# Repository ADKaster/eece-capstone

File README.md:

# eece-capstone
Repository to store software work products for capstone.

## Project Overview

The communication library is the Distributed Microcontroller Communication Framework Library (dmcflib for short).

The end goal is to enable an application developer to use the publish-subscribe API presented in the library to easily send messages
between different microcontrollers in a system over I2C. The real demo application will be a telemetry system for an amateur rocket
with a Sensor, Data Logging, Power and Radio Communcations board. The project will be implemented using the TI Simplelink family
of ARM Cortex-M4F microcontrollers, with 3 MSP432s and one CC1310 Sub-1GHz MCU. 

## Configuration

Initial compilation and environment setup was tested using Ubuntu 14.04 LTS in an Oracle 
VirtualBox Virtual Machine, as well as Windows 10.

Theere are two main dependencies for this project. Code Composer Studio, and FreeRTOS.

### Code Composer Studio

The project requires TI's Code Composer Stuido Version 7 (ccsv7). This is necessary for
the cross-compiler as well as TI's SimpleLink SDK.

* Download Code composer studio version 7.x [here](http://processors.wiki.ti.com/index.php/Download_CCS)
* Ensure that Code Composer studio will be installed at ~/ti (or $HOME/ti or /home/<username>/ti) on linux, or C:/ti on Windows.
* Click the two checkboxes for SimpleLink MSP432 and SimpleLink CC13XX support.
* Perform all  other installation steps per TI's wiki as linked above
* On the "Getting Started" page, click the "Browse Examples" option to open the Resource Explorer. Alternatively, if the Resource Explorer is already open, navigate to that tab.
* Open the tree on the left side of the Resource Explorer titled "Software"
* Click the button that looks like a download button and download the MSP432 SDK v:1.60.00.12 "offline"

### FreeRTOS

FreeRTOS is used to manage task scheduling

* Download FreeRTOSv10.0.0 [here](http://www.freertos.org/a00104.html)
* Extract the archive to either your home directory on linux, or c:/ on Windows

### Adding the projects to Code Composer Studio

Steps to start working:
 
 * Clone the git repository to your favorite location

 * Download ccsv7 with MSP432 and CC13xx libraries
 	* /home/user/ti
 	* c:\ti
 
 * Install MSP432 simplelink sdk v1.60.00.12 from resource explorer
 
 * Install FreeRTOSv10.0.0
 	* /home/user/FreeRTOSv10.0.0
 	* c:\FreeRTOSv10.0.0
 
 * Open CCS and create a workspace in the same directory as the git repo
 
 * Go to Window-->Preferences-->General-->Workspace-->Linked Resources
     * New, Name = FREERTOS_INSTALL_DIR, Location = FreeRTOS Install Folder (with the vXX.XX.XX)
	 
 * Go to Project-->Import CCS Projects
     * Click Browse, Ok (Defaults to workspace directory)
	 * Check box next to all projects, click finish

 * Build the MSP432_example project, or your favorite application project	 
	
## Caveats
* Only configured to build for the MSP432. Additional tweaks and setup required to support CC13x0 boards. :(

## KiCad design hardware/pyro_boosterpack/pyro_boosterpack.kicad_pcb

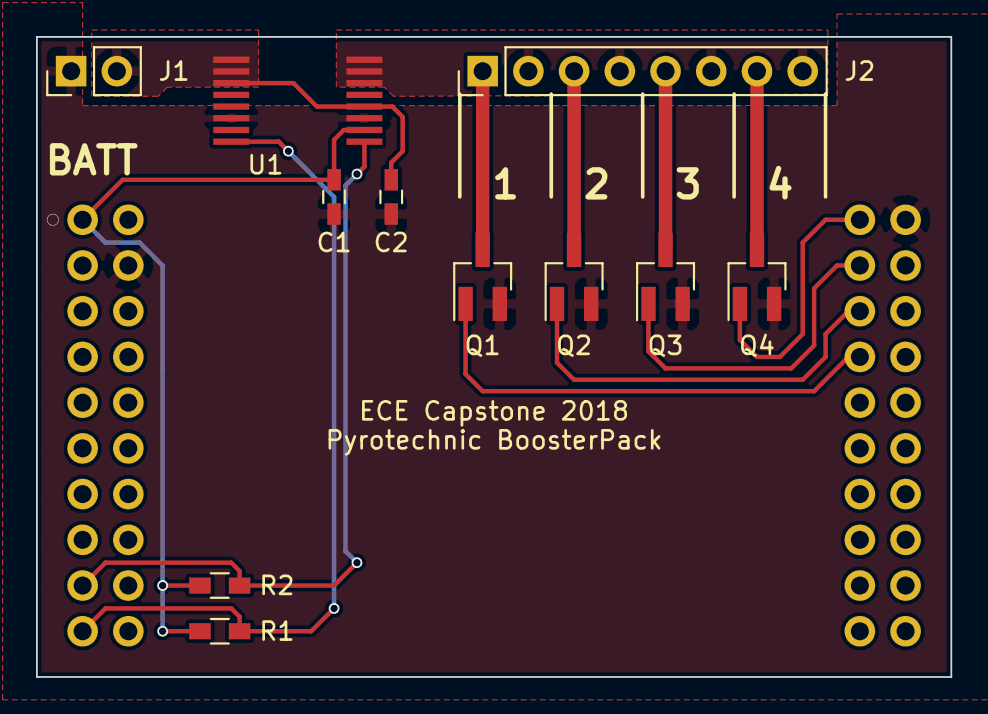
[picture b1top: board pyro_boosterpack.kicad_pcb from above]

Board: 2 copper layers, 50.8 x 35.6 mm, 12 parts (0 on the bottom side), 14 nets.

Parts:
C1, C2: 0.1uF; C_0603_HandSoldering
J1: Conn_01x02; Pin_Header_Straight_1x02_Pitch2.54mm
J2: Conn_01x08; Pin_Header_Straight_1x08_Pitch2.54mm
J3: Conn_01x40; ti_boosterpack_40pin
Q1, Q2, Q3, Q4: Q_NMOS_GSD; SOT-23_Handsoldering
R1, R2: 4.7k; R_0603_HandSoldering
U1: ina260; tssop-16

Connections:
+3V3: C1.2, J3.1, R1.1, R2.1, U1.10
+BATT: C2.2, J1.2, U1.1, U1.2, U1.3, U1.12
/BATT_LOAD: J2.2, J2.4, J2.6, J2.8, U1.14, U1.15, U1.16
/PYRO_1_EN: J3.37, Q1.1
/PYRO_1_OUT: J2.1, Q1.3
/PYRO_2_EN: J3.38, Q2.1
/PYRO_2_OUT: J2.3, Q2.3
/PYRO_3_EN: J3.39, Q3.1
/PYRO_3_OUT: J2.5, Q3.3
/PYRO_4_EN: J3.40, Q4.1
/PYRO_4_OUT: J2.7, Q4.3
/SCL: J3.9, R2.2, U1.9
/SDA: J3.10, R1.2, U1.8
GND: C1.1, C2.1, J1.1, J3.20, J3.22, Q1.2, Q2.2, Q3.2, Q4.2, U1.6, U1.11

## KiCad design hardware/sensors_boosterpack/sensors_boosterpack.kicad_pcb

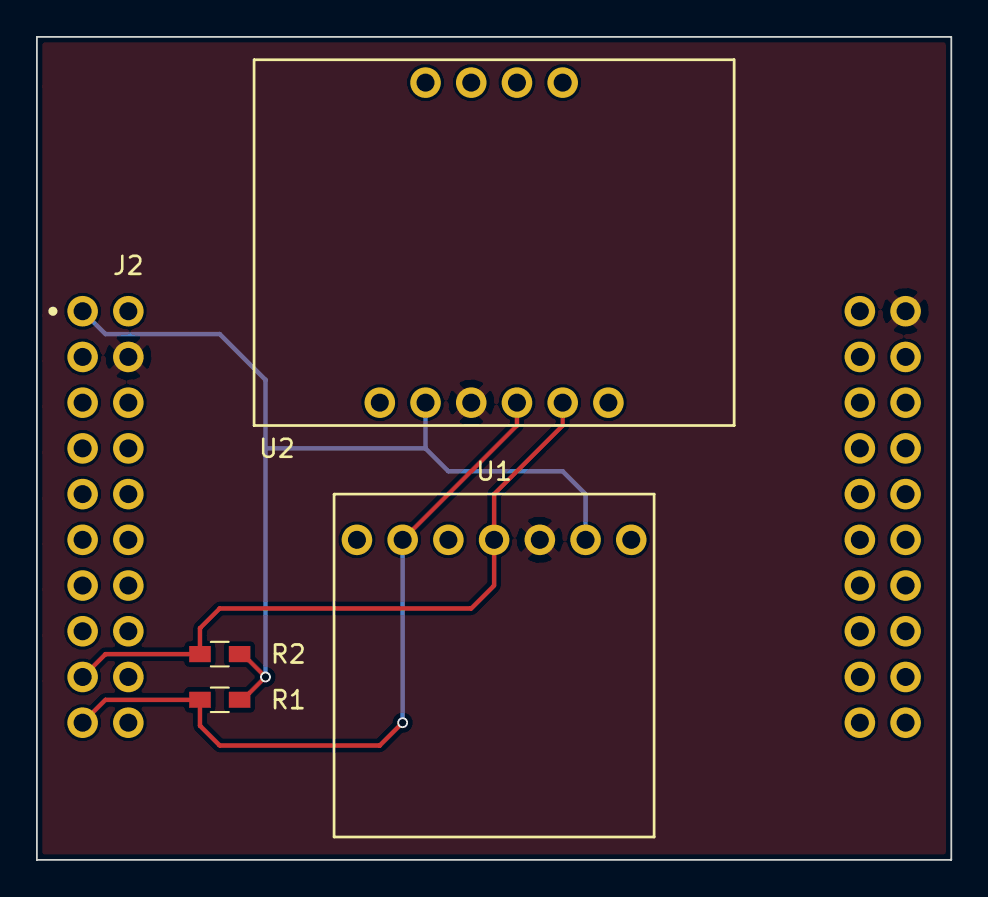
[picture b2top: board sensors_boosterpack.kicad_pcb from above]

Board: 2 copper layers, 50.8 x 45.7 mm, 5 parts (0 on the bottom side), 4 nets.

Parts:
J2: Conn_01x40; ti_boosterpack_40pin
R1, R2: 4.7k; R_0603_HandSoldering
U1: adafruit_bmp280
U2: adafruit_bno055

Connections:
+3V3: J2.1, R1.1, R2.1, U1.2, U2.2
/SCL: J2.9, R2.2, U1.4, U2.5
/SDA: J2.10, R1.2, U1.6, U2.4
GND: J2.20, J2.22, U1.3, U2.3

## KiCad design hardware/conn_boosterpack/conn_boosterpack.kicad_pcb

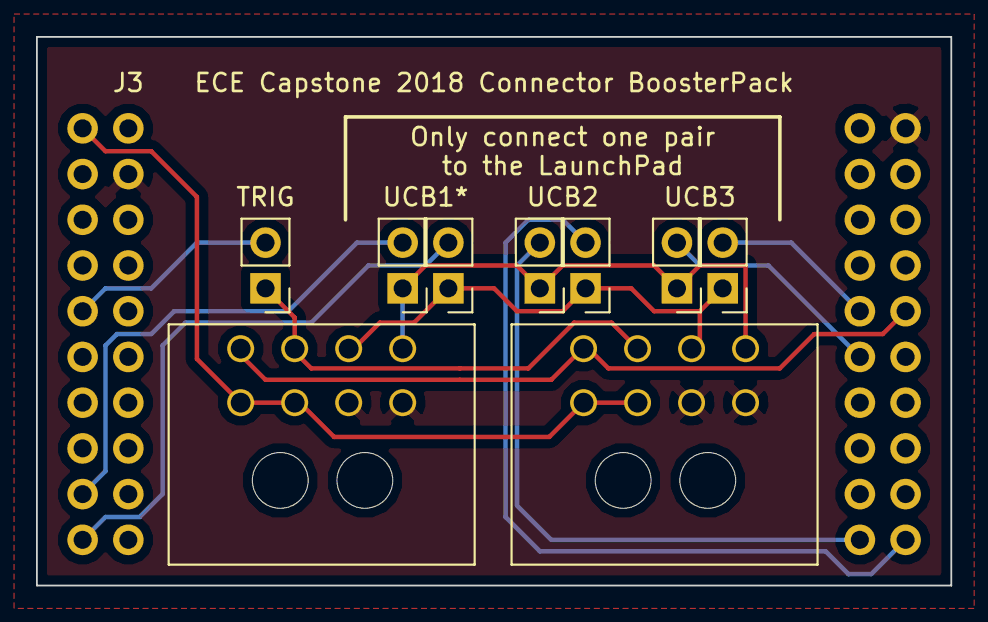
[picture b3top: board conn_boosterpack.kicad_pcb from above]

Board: 2 copper layers, 50.8 x 30.5 mm, 10 parts (0 on the bottom side), 13 nets.

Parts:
J1, J2: Conn_01x08; Molex_Microfit3_Header_02x04_Angled_43045-080x
J3: Conn_01x40; ti_boosterpack_40pin
JP1, JP2, JP3, JP4, JP5, JP6, JP7: Jumper; Pin_Header_Straight_1x02_Pitch2.54mm

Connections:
+3V3: J1.3, J1.4, J2.3, J2.4, J3.1
/GPIO_P5: J3.5, JP7.2
/RST: J1.8, J2.8, J3.16
/SCL: J1.5, J2.5, JP1.1, JP3.1, JP5.1
/SDA: J1.6, J2.6, JP2.1, JP4.1, JP6.1
/TRIG: J1.7, J2.7, JP7.1
/UCB1_SCL: J3.9, JP1.2
/UCB1_SDA: J3.10, JP2.2
/UCB2_SCL: J3.31, JP3.2
/UCB2_SDA: J3.11, JP4.2
/UCB3_SCL: J3.35, JP5.2
/UCB3_SDA: J3.36, JP6.2
GND: J1.1, J1.2, J2.1, J2.2, J3.20, J3.22

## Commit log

2017-06-18 add skeleton message def config files
2017-06-19 Add doxygen comments
2017-06-19 Fix up makefile
2017-06-21 add demo msp432 application
2017-06-21 Make it so TI's building of FreeRTOS uses the includes.mak from the project
2017-06-21 Make remake more consistent
2017-06-21 Prettyify build output
2017-06-21 Add more demo applications
2017-06-28 More comments, more modular, more fun
2017-06-29 start to add README instructions
2017-06-30 Windows testing oh god please help
2017-06-30 now works with CCSv7.2
2017-06-30 Make now works on windows :~)
2017-08-03 Implement i2c for msp432 with skeleton. changes to allow latest version of ccsv7 tools.
2017-08-03 Use unix line endings >:(
2017-08-03 Add Eclipse Configuration Instructions to README, more line ending fixes
2017-08-03 Make README.md additions proper markdown
2017-08-05 Convert to POSIX in library. Add Example application (that runs! :D). I2C functionality not exercised in example yet.
2017-08-07 Line endings, implement ring buffer for i2c slave, implement i2c slave state machine, implement custom i2c slave isr to handle ring buffer
2017-08-08 add messaging helper functions, add dependency generation to CFLAGS
2017-08-08 implement more of i2c slave state machine. minor fixes to app main, whitespace/newline issues. More comments
2017-08-12 Implement i2c master fixups, modularize slave fixups
2017-08-26 communications library Updates per diagrams
2017-08-26 add visio drawings
2017-08-27 Begin implementing high level pubsub features
2017-08-27 Implement sub_get and pub_put
2017-09-02 Moved MSP432 project to specific directory to make room for cc13xx files later
2017-09-08 Implement Slave packet responses
2017-09-08 Implement example with ping message for testing
2017-09-17 add configuration for multiple nodes to example
2017-09-17 changed config.mak to define APPXXX instead of APPLICATIONWHOAMI directly
2017-11-17 Add Project description to README
2018-01-10 Update README.md
    For latest tool versions
2018-01-10 Upgrade to new SDK Version
2018-01-16 First attempt
2018-01-16 Put workspace in git repo
2018-01-16 update gitignore
2018-01-16 gitignore again
2018-01-16 re-add .metatdata
2018-01-16 More workspace stuff
2018-01-16 create all projects, not building yet
2018-01-18 Working project, remove all residual eclipse files
2018-01-18 Update Makefile for latest procedure
2018-01-18 Remove more eclipse stuff, change application definition to be entirely app controlled
2018-01-18 remove more eclipse stuff
2018-01-18 remove even more eclipse stuff
2018-01-18 Use libc_nano.a exclusively instead of libc.a
2018-01-19 Update README.md to fix typos and inconsistencies
2018-01-19 Rename library to DMCF, fix typos
2018-01-23 remove unused file
2018-01-23 Add project bar, in middle of testing.
2018-01-25 more changes, add debug printf wrapper and do way too much coupling b/w projects
2018-01-25 Actually transmit to broadcast address for broadcast messages. Investigate with logic analyzer next
2018-01-26 added google test files
2018-01-29 Enable READ interrupts for slave on startup and on completion of transactions: always want to be listening
2018-01-30 retry unitTest ccs project with gtest library folder
2018-01-30 Added nonfuctioning unit test
2018-01-30 rework I2C Slave to not use ring buffer anymore -- not necessary
2018-01-31 Debugging more, get messages now. mqueue length wrong for broadcast, need to remove sizeof(bool)
2018-02-02 initial commit of hardware
2018-02-06 Finished rev 2 of the connector boosterpack
2018-02-06 Final commit of nonworking Google Test Code
2018-02-06 Nonworking gtest directory shelving for now
2018-02-06 Working broadcast with one publisher and one subscriber
2018-02-06 Two publishers, two subscribers working. Neat.
2018-02-07 Add working c++ example project
2018-02-09 Library compiles without warnings in C++. Linking is next
2018-02-09 Build applications without errors. Only warnings in FreeRTOS project, but who cares, that's c++ for you.
2018-02-09 Add changes for tested C++ port
2018-02-09 Add application choosing of I2C Busses
2018-02-11 first commit of pyro board
2018-02-11 New and improved pyro boosterpack pcb - ship it
2018-02-11 Updated gitignore to ignore kicad backup files
2018-02-14 Added INA260 to pyro board
2018-02-14 Forgot to assign C2 its label
2018-02-15 include adafruit bmp280 library, comment out commincation code relating to SPI todo: reimplement i2c functions, set up demo to collect data from sensor
2018-02-20 fix SPI and math library errors
2018-02-27 library compiles!
2018-02-28 Added gitattributes to fix line endings
2018-02-28 PyroDriver class working with c interfaces
2018-02-28 Switch from using UCB0 and UCB1 to using UCB1 and UCB2
2018-02-28 Switch from using UCB0 and UCB1 to using UCB1 and UCB2
    (cherry picked from commit 8b95bfb5a295694a125f15ecb8da969a07bd6bd0)
2018-03-01 Added original Adafruit BNO055 files
2018-03-01 Cleanup and check for NULL pointer in slave callback
2018-03-14 current progress not working
2018-03-15 separate example project for pulling altimiter data
2018-03-15 Initial draft, pulling altimeter data and displaying temp, pressure and altitude
2018-03-15 It generates data! Thanks Andrew
2018-03-20 Fixed hole sizes (ugh)
2018-03-20 Victory! Sensor readout works and makes sense
2018-03-21 Made changes based on feedback
2018-03-21 Cleanup and fix activation steps. Make demo make more sense
2018-03-21 Fix bounds check on activate
2018-03-21 Reorder Pyro GPIOs to correspond to names on PCB, fix pin for first pyro
2018-03-22 Cleanup pyro driver based on more code review
2018-03-27 Fix line endings for dmcf_debug.h
2018-03-28 working example to get data from bno055
2018-03-29 Inital changes with pyro and altimeter, before testing
2018-03-29 Increase stack size, remove custom i2c master ISR since its unecessary. Weird line ending fixes that don't make any damn sense why they won't reset.
2018-03-29 Remove excessive debug info
2018-03-30 Rename to Node_IMU
2018-03-30 Modify Node_IMU for work with the system
2018-03-30 Fix compiler warnings, fix I2C slave adddress for IMU node
2018-03-30 Initial port of TI's example code
2018-03-30 Changes, something is wrong with writes. Reads work as if the chip is programmed with the actual TI example it works fine
2018-03-30 super finniky, something wrong with timing?
2018-03-30 Enable watchdog and reset if we fail to intialize the battery monitor chip :D. If it works it works right?
2018-04-05 Very first pass on an animated graph that reads csv data from a serial connection and plots that data
2018-04-05 idk, some config changes or something
2018-04-05 Testing with proper node names, merge altimeter and IMU code as they are on the same breakout
2018-04-05 Tested, works so don't touchy
2018-04-05 Rename to node battery
2018-04-05 Commit useless line endings because I juast want to damn merge
2018-04-05 mid-testing. not working
2018-04-06 Working example of two independent animating graphs
2018-04-06 make a separate function for trimming data sets, for less code repetition
2018-04-06 add a setup script for easy installation for required packages have python installed, navigate to the directory, and run the following commands: `setup.py build` `setup.py install`
2018-04-09 final pls
2018-04-10 let's make a commit now that serial processing mostly works
2018-04-10 use separate thread for serial data collection
2018-04-10 Fix line ending snafu
2018-04-10 It just has to work tomorrow
2018-04-18 aesthetique changes
